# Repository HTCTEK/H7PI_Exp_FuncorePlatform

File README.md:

# H7PI_Exp_FuncorePlatform

### What is H7PI_Exp_FuncorePlatform
An expansion board for H7PI(STM32H7) users who are used to developing on Funcore, such as light sensor, temperature sensor and so on.

### How to use
1. Buy Funcore modules that you want to develop with.
2. Buy a H7PI_Exp_FuncorePlatform and install H7PI on it.
3. Download H7PI_Samples and load Funcore drivers.
4. Compile the project and download axf wiht mdk keil.
5. wiki-->[click]().

### Pictures

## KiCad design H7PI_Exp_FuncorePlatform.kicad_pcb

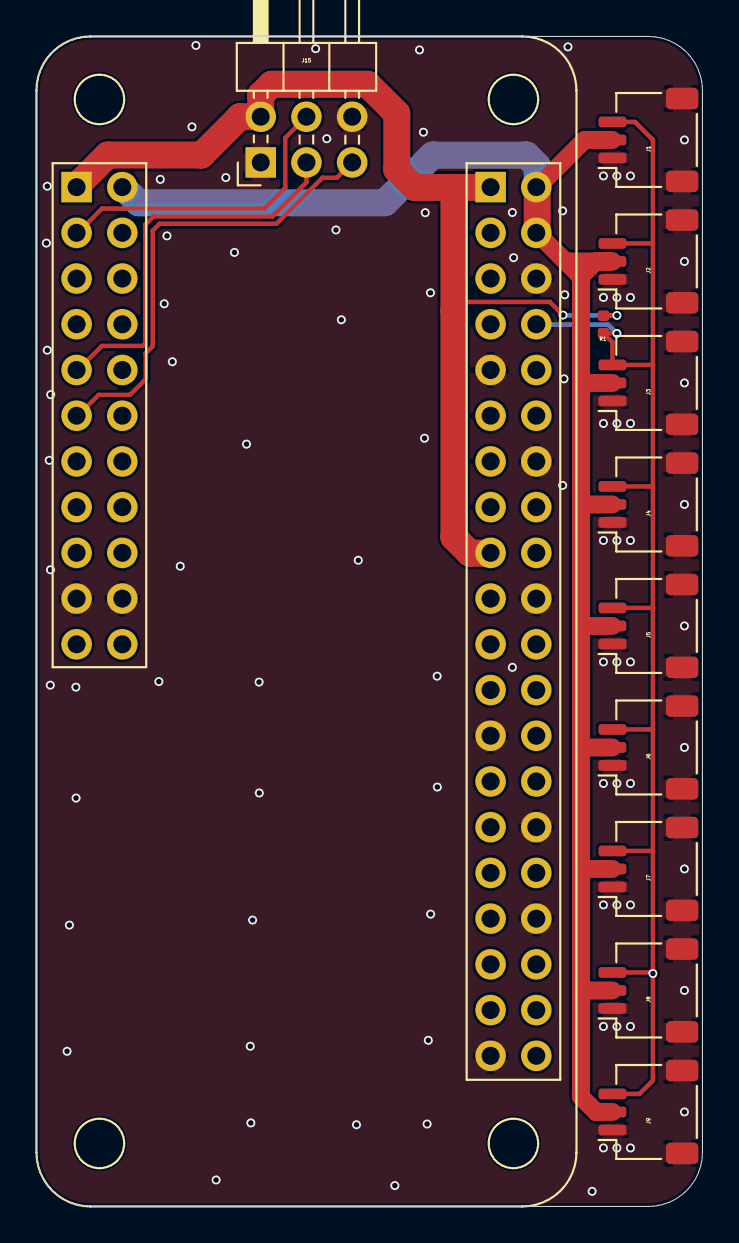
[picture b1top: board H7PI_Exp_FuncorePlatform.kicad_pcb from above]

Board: 2 copper layers, 37.0 x 65.0 mm, 12 parts (0 on the bottom side), 7 nets.

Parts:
J1, J2, J3, J4, J5, J6, J7, J8, J9: A1002WR-S-3P; JST_SH_SM03B-SRSS-TB_1x03-1MP_P1.00mm_Horizontal
J15: Header_2x3; PinHeader_2x03_P2.54mm_Horizontal
R1: DNP; R_0402_1005Metric
U1: H7PI_Exp; Module_H7PI_Exp_65x30mm

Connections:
/3V3: J15.2, R1.1, U1.1, U1.21, U1.37
/BOOT: J15.4, U1.3
/SIG: J1.3, J2.3, J3.3, J4.3, J5.3, J6.3, J7.3, J8.3, J9.3, R1.2, U1.28
/SWDCLK: J15.5, U1.11
/SWDIO: J15.3, U1.9
/VBUS: J1.2, J2.2, J3.2, J4.2, J5.2, J6.2, J7.2, J8.2, J9.2, U1.2, U1.22, U1.24
GND: J1.1, J1.MP, J2.1, J2.MP, J3.1, J3.MP, J4.1, J4.MP, J5.1, J5.MP, J6.1, J6.MP, J7.1, J7.MP, J8.1, J8.MP, J9.1, J9.MP, J15.1, J15.6, U1.19, U1.20, U1.26, U1.29, U1.34, U1.40, U1.45, U1.50, U1.54, U1.59

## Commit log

2020-01-09 update license to BSD
2020-01-09 v0.1 push
